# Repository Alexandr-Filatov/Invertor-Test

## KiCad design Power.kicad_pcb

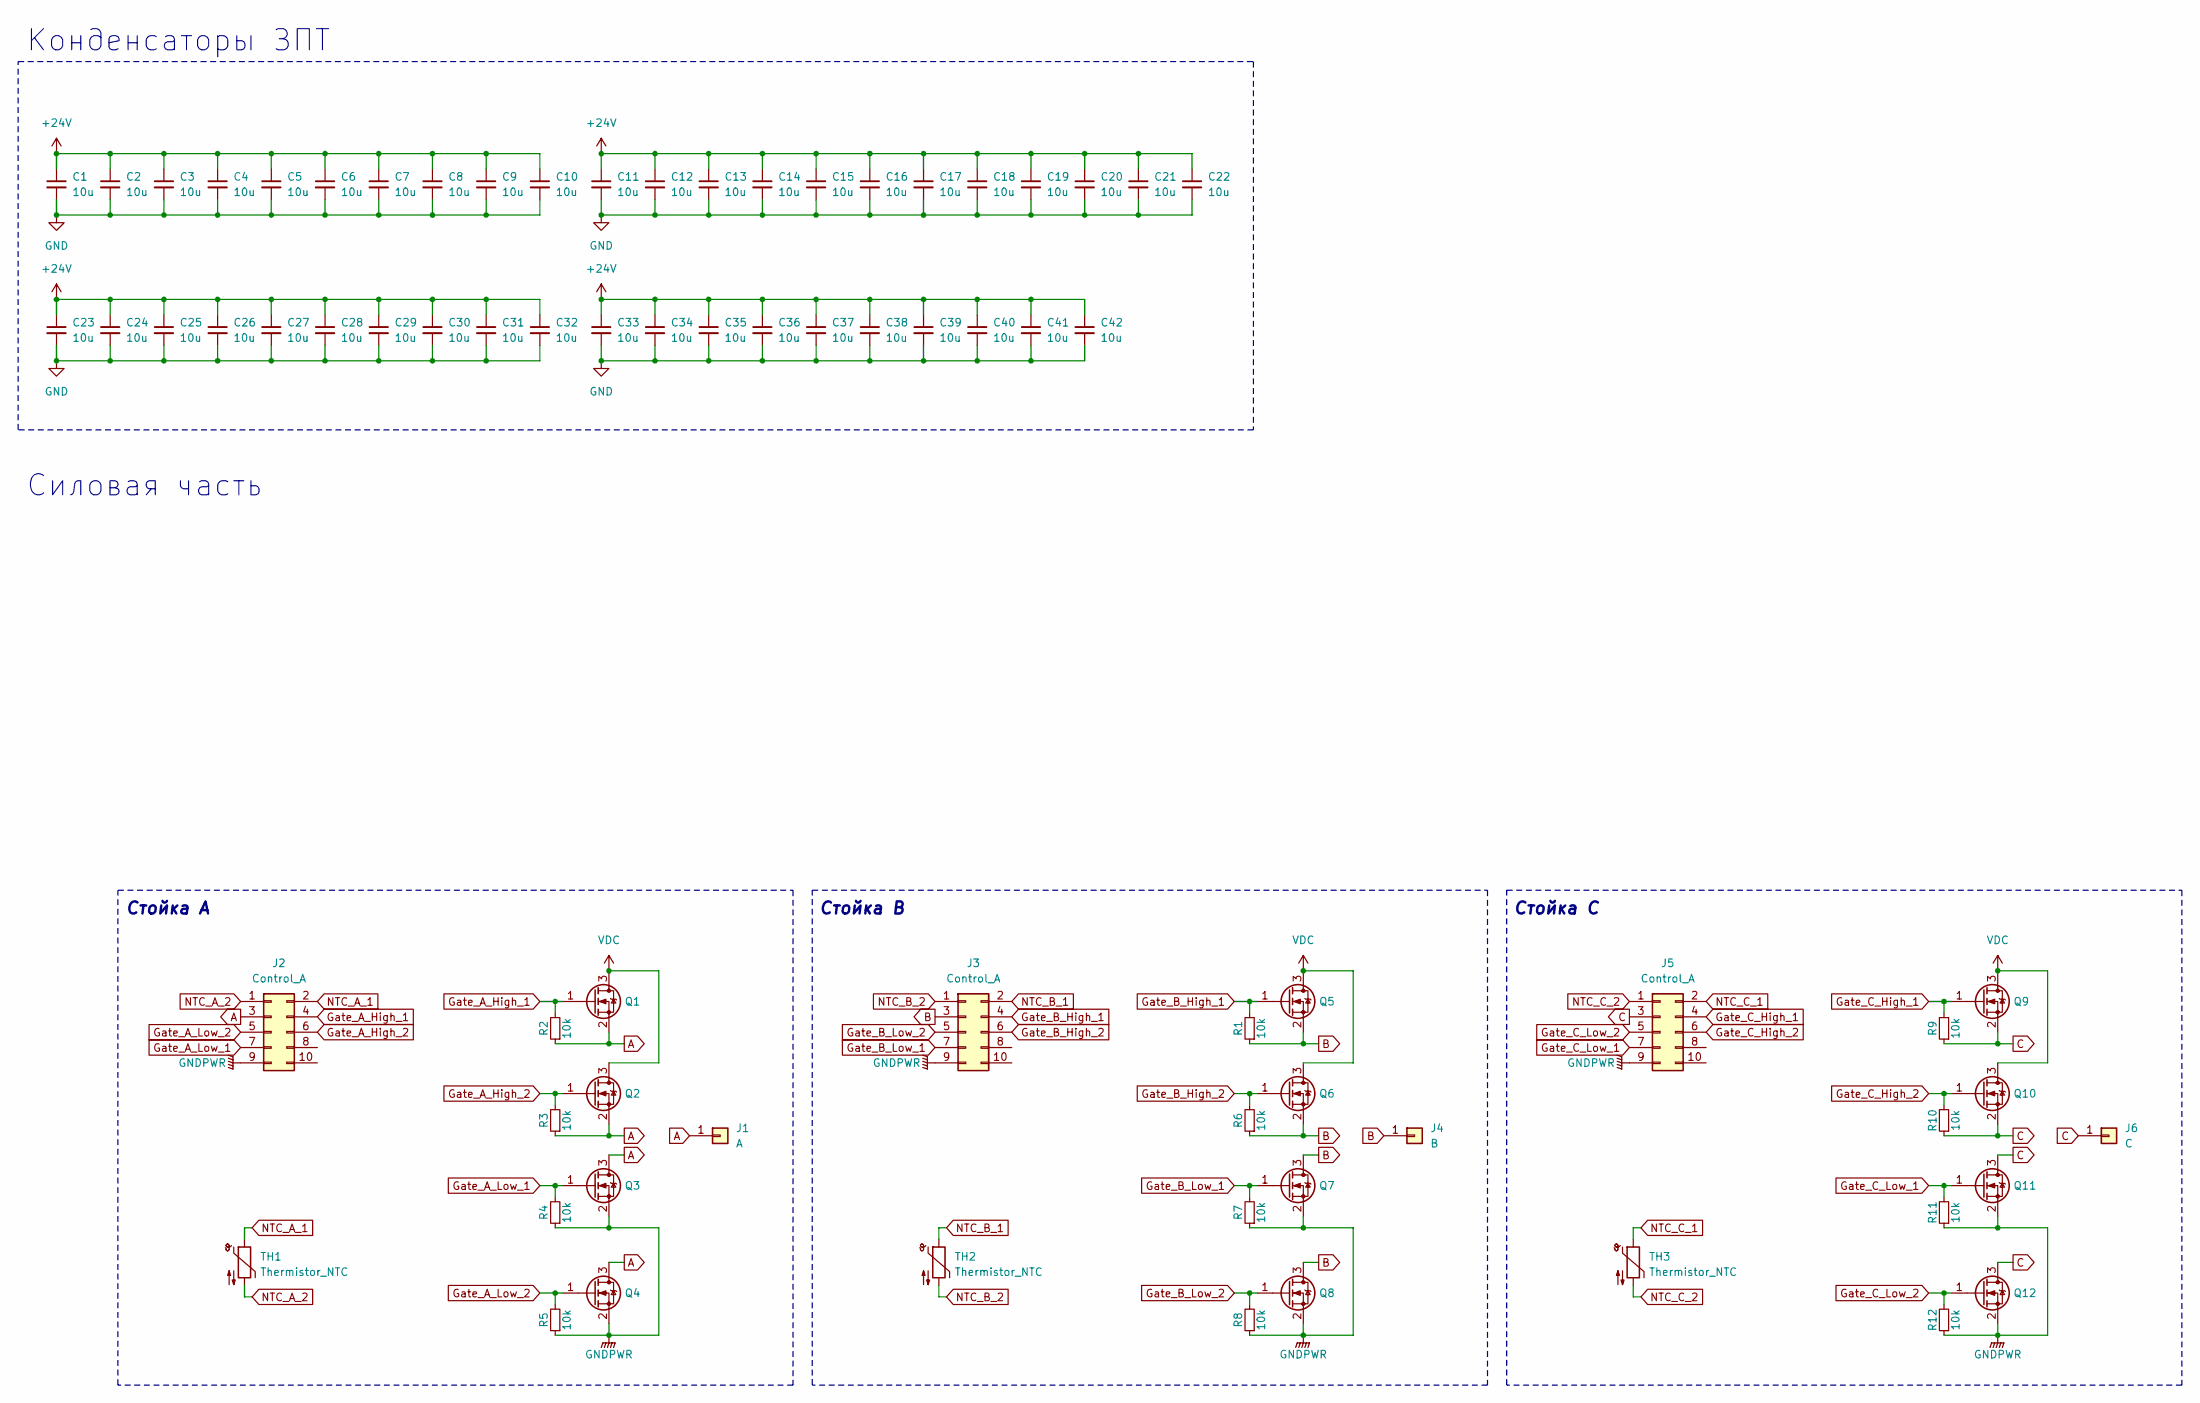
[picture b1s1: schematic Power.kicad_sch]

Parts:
C1, C2, C3, C4, C5, C6, C7, C8, C9, C10, C11, C12, C13, C14, C15, C16, C17, C18, C19, C20, C21, C22, C23, C24, C25, C26, C27, C28, C29, C30, C31, C32, C33, C34, C35, C36, C37, C38, C39, C40, C41, C42: 10u; C_1210_3225Metric_Pad1.33x2.70mm_HandSolder
J1: A; Bush_M4
J2, J3, J5: Control_A; 11882750
J4: B; Bush_M4
J6: C; Bush_M4
Q1, Q2, Q3, Q4, Q5, Q6, Q7, Q8, Q9, Q10, Q11, Q12: 2N7002; IPTG007N06NM5ATMA1
R1, R2, R3, R4, R5, R6, R7, R8, R9, R10, R11, R12: 10k; R_0805_2012Metric_Pad1.20x1.40mm_HandSolder
TH1, TH2, TH3: Thermistor_NTC; R_0603_1608Metric_Pad0.98x0.95mm_HandSolder

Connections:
+24V: C1.1, C2.1, C3.1, C4.1, C5.1, C6.1, C7.1, C8.1, C9.1, C10.1, C11.1, C12.1, C13.1, C14.1, C15.1, C16.1, C17.1, C18.1, C19.1, C20.1, C21.1, C22.1, C23.1, C24.1, C25.1, C26.1, C27.1, C28.1, C29.1, C30.1, C31.1, C32.1, C33.1, C34.1, C35.1, C36.1, C37.1, C38.1, C39.1, C40.1, C41.1, C42.1
A: J1.1, J2.3, Q1.2 (S), Q2.2 (S), Q3.3 (D), Q4.3 (D), R2.1, R3.1
B: J3.3, J4.1, Q5.2 (S), Q6.2 (S), Q7.3 (D), Q8.3 (D), R1.1, R6.1
C: J5.3, J6.1, Q9.2 (S), Q10.2 (S), Q11.3 (D), Q12.3 (D), R9.1, R10.1
GND: C1.2, C2.2, C3.2, C4.2, C5.2, C6.2, C7.2, C8.2, C9.2, C10.2, C11.2, C12.2, C13.2, C14.2, C15.2, C16.2, C17.2, C18.2, C19.2, C20.2, C21.2, C22.2, C23.2, C24.2, C25.2, C26.2, C27.2, C28.2, C29.2, C30.2, C31.2, C32.2, C33.2, C34.2, C35.2, C36.2, C37.2, C38.2, C39.2, C40.2, C41.2, C42.2
GNDPWR: J2.9, J3.9, J5.9, Q3.2 (S), Q4.2 (S), Q7.2 (S), Q8.2 (S), Q11.2 (S), Q12.2 (S), R4.1, R5.1, R7.1, R8.1, R11.1, R12.1
Gate_A_High_1: J2.4, Q1.1 (G), R2.2
Gate_A_High_2: J2.6, Q2.1 (G), R3.2
Gate_A_Low_1: J2.7, Q3.1 (G), R4.2
Gate_A_Low_2: J2.5, Q4.1 (G), R5.2
Gate_B_High_1: J3.4, Q5.1 (G), R1.2
Gate_B_High_2: J3.6, Q6.1 (G), R6.2
Gate_B_Low_1: J3.7, Q7.1 (G), R7.2
Gate_B_Low_2: J3.5, Q8.1 (G), R8.2
Gate_C_High_1: J5.4, Q9.1 (G), R9.2
Gate_C_High_2: J5.6, Q10.1 (G), R10.2
Gate_C_Low_1: J5.7, Q11.1 (G), R11.2
Gate_C_Low_2: J5.5, Q12.1 (G), R12.2
NTC_A_1: J2.2, TH1.1
NTC_A_2: J2.1, TH1.2
NTC_B_1: J3.2, TH2.1
NTC_B_2: J3.1, TH2.2
NTC_C_1: J5.2, TH3.1
NTC_C_2: J5.1, TH3.2
VDC: Q1.3 (D), Q2.3 (D), Q5.3 (D), Q6.3 (D), Q9.3 (D), Q10.3 (D)

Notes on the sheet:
Стойка А
Стойка B
Силовая часть
Конденсаторы ЗПТ
Стойка C

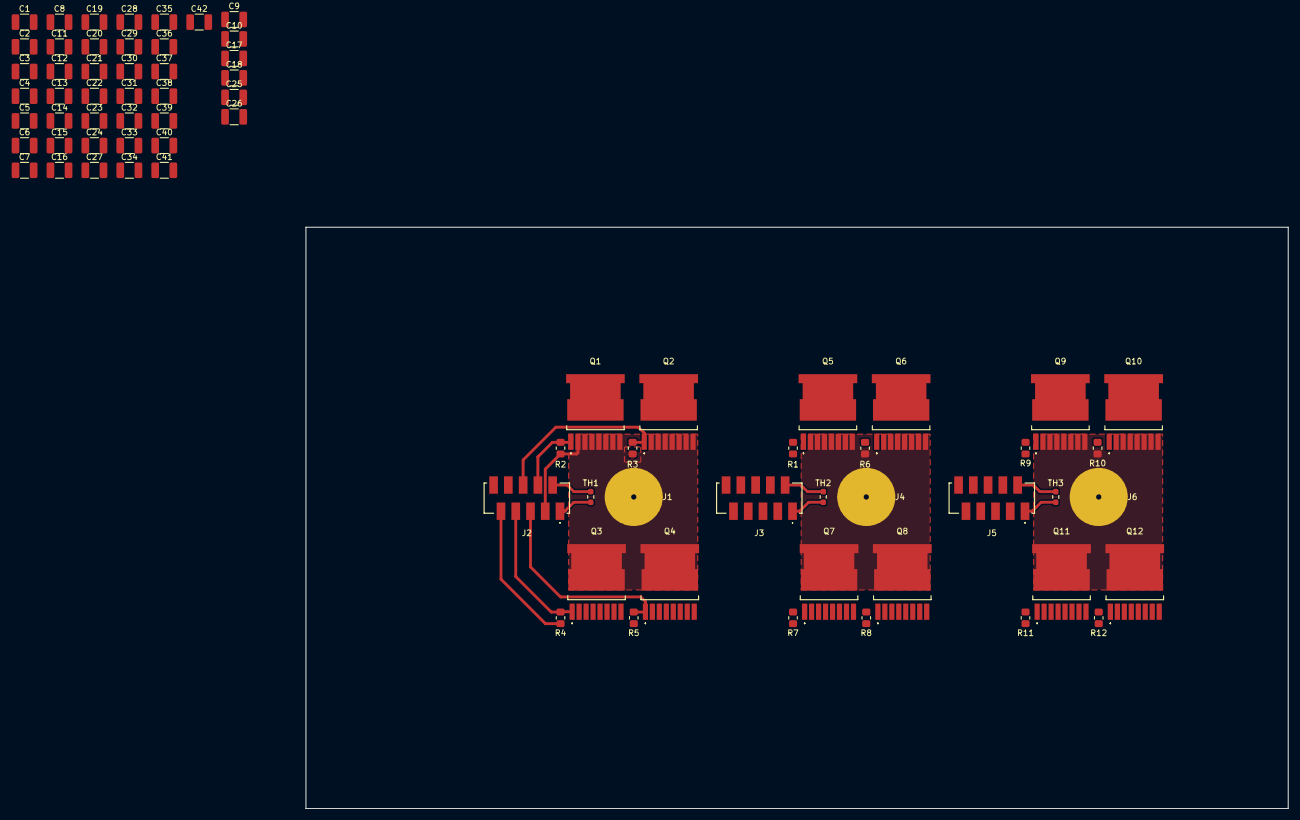
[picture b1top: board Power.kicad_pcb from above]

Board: 2 copper layers, 169.0 x 100.0 mm, 75 parts (0 on the bottom side), 25 nets.

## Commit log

2024-11-04 Zero commit
